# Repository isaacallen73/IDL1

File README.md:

# _Sample project_

(See the README.md file in the upper level 'examples' directory for more information about examples.)

This is the simplest buildable example. The example is used by command `idf.py create-project`
that copies the project to user specified path and set it's name. For more information follow the [docs page](https://docs.espressif.com/projects/esp-idf/en/latest/api-guides/build-system.html#start-a-new-project)

## How to use example
We encourage the users to use the example as a template for the new projects.
A recommended way is to follow the instructions on a [docs page](https://docs.espressif.com/projects/esp-idf/en/latest/api-guides/build-system.html#start-a-new-project).

## Example folder contents

The project **sample_project** contains one source file in C language [main.c](main/main.c). The file is located in folder [main](main).

ESP-IDF projects are built using CMake. The project build configuration is contained in `CMakeLists.txt`
files that provide set of directives and instructions describing the project's source files and targets
(executable, library, or both). 

Below is short explanation of remaining files in the project folder.

```
├── CMakeLists.txt
├── main
│   ├── CMakeLists.txt
│   └── main.c
└── README.md                  This is the file you are currently reading
```
Additionally, the sample project contains Makefile and component.mk files, used for the legacy Make based build system. 
They are not used or needed when building with CMake and idf.py.

## Android app

This repository also contains an Android application in the `android-app/` folder. The Android project is included for convenience and should be built from Android Studio or the Gradle wrapper.

- Do NOT commit `local.properties` or keystore files (`*.jks`, `*.keystore`). A project-level `.gitignore` is present to prevent accidental commits of these files.
- To build locally, create `local.properties` (not checked in) containing your Android SDK path, for example:

```
sdk.dir=C:/Users/isaac/AppData/Local/Android/Sdk
```

- Open the `android-app` folder in Android Studio or run the Gradle wrapper from the `android-app` folder:

```powershell
cd android-app
.\gradlew assembleDebug
```

- The repo-level `.gitignore` ignores `android-app/build/` and other generated files.

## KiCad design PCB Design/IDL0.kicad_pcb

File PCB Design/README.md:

# PCB Design for Mountain Bike Datalogger

This directory contains everything needed to design and manufacture the PCB for the mountain bike datalogger project.

---

## Quick Links

| Document | Purpose |
|----------|---------|
| **[QUICK_START.md](QUICK_START.md)** | Start here! Step-by-step guide to generate your PCB |
| **[PROGRAMMATIC_PCB_TOOLS.md](PROGRAMMATIC_PCB_TOOLS.md)** | Complete research on CLI/Python PCB tools |
| **[pnan.md](pnan.md)** | Complete circuit specification and netlist |
| **[KICAD_WORKFLOW.md](KICAD_WORKFLOW.md)** | Manual KiCad design workflow |
| **[DESIGN_CHECKLIST.md](DESIGN_CHECKLIST.md)** | Pre-manufacturing verification checklist |

---

## What's in This Directory

### Documentation Files

1. **QUICK_START.md** - Your starting point
   - Three workflow options (automated, semi-automated, manual)
   - Step-by-step walkthrough
   - Troubleshooting guide
   - Complete from netlist generation to ordering PCBs

2. **PROGRAMMATIC_PCB_TOOLS.md** - Tool research and comparison
   - kicad-cli capabilities and examples
   - SKiDL for Python-based schematic entry
   - pcbnew Python API for PCB manipulation
   - FreeRouting autorouter integration
   - PCBflow for programmatic routing
   - PHDL hardware description language
   - Complete workflow options with pros/cons
   - Installation instructions

3. **pnan.md** - Circuit specification
   - Complete netlist and pin assignments
   - Power distribution
   - Component list
   - Connector pinouts
   - PCB layout guidelines
   - Bill of materials

4. **KICAD_WORKFLOW.md** - Manual KiCad workflow
   - Traditional PCB design process
   - Best practices for KiCad
   - Layer stack configuration
   - Design rules

5. **DESIGN_CHECKLIST.md** - Pre-manufacturing checklist
   - Component placement verification
   - Routing checks
   - DRC validation
   - Gerber export checklist

### Python Scripts

1. **generate_pcb.py** - Circuit definition and netlist generator
   - Complete datalogger circuit in SKiDL
   - Generates KiCad-compatible netlist
   - Creates component placement helper script
   - Provides workflow examples
   - **Run this first!**

2. **autoroute_example.py** - Automation and export tools
   - FreeRouting integration
   - DRC automation
   - Gerber export automation
   - Position file generation
   - 3D model export

---

## Getting Started

### Option 1: Quick Start (Recommended)

```bash
# Install dependencies
pip install skidl

# Generate circuit and netlist
python generate_pcb.py

# Follow the steps in QUICK_START.md
```

### Option 2: Read First, Then Build

1. Read **PROGRAMMATIC_PCB_TOOLS.md** to understand the tools
2. Review **pnan.md** to understand the circuit
3. Follow **QUICK_START.md** for step-by-step instructions

### Option 3: Traditional Workflow

1. Read **KICAD_WORKFLOW.md**
2. Use **pnan.md** as reference
3. Design manually in KiCad GUI
4. Use **DESIGN_CHECKLIST.md** before ordering

---

## Workflow Comparison

### Fully Automated (Experimental)
- **Tools**: SKiDL + pcbnew API + FreeRouting + kicad-cli
- **Automation**: ~80%
- **Quality**: Good
- **Time**: 1-2 hours
- **Best for**: Simple boards, rapid prototyping, learning

### Semi-Automated (Recommended)
- **Tools**: SKiDL + Manual KiCad + FreeRouting + kicad-cli
- **Automation**: ~40%
- **Quality**: Excellent
- **Time**: 2-4 hours
- **Best for**: Production boards, this datalogger

### Manual with Scripts
- **Tools**: SKiDL (netlist only) + Manual KiCad + kicad-cli
- **Automation**: ~20%
- **Quality**: Excellent
- **Time**: 4-6 hours
- **Best for**: Learning KiCad, complex boards

---

## File Outputs

When you run `generate_pcb.py`, it creates:

```
output/
├── datalogger.net          # KiCad netlist (import to PCBNew)
├── place_components.py     # Component placement script
└── README.txt              # Next steps

```

When you run `autoroute_example.py export`, it creates:

```
output/
├── gerbers/
│   ├── *.gbr               # Gerber files (one per layer)
│   ├── *.drl               # Drill files
│   └── *-job.gbrjob        # Gerber job file
├── datalogger_pos.csv      # Component position file
├── datalogger.step         # 3D STEP model
└── drc_report.txt          # Design rule check report
```

---

## Key Technologies Used

### 1. SKiDL (Schematic Capture)
Python package for circuit definition
- Website: https://devbisme.github.io/skidl/
- GitHub: https://github.com/devbisme/skidl
- Install: `pip install skidl`

### 2. KiCad (PCB Design)
Open-source EDA software
- Website: https://www.kicad.org/
- Docs: https://docs.kicad.org/
- Version: 8.0 or 9.0 recommended

### 3. kicad-cli (Command Line Interface)
Built into KiCad 7+
- Export Gerbers
- Run DRC
- Generate documentation
- No separate installation needed

### 4. FreeRouting (Autorouter)
Open-source PCB autorouter
- Website: https://freerouting.org/
- GitHub: https://github.com/freerouting/freerouting
- Install: Via KiCad Plugin Manager

### 5. pcbnew Python API (Optional)
KiCad's Python scripting interface
- Built into KiCad
- Cross-version wrapper: `pip install kicad-python`
- Docs: https://dev-docs.kicad.org/

---

## Circuit Overview

**Main Components:**
- Seeed XIAO ESP32-C6 (microcontroller)
- 3x BMI160 IMU (onboard + front + rear)
- NEO-6M GPS module
- microSD card slot
- JST battery connector
- 3x waterproof connectors (front, rear, handlebar)

**Key Features:**
- SPI bus for sensors and SD card
- UART for GPS
- Analog inputs for pressure sensors
- GPIO for buttons and LED
- Complete power distribution with decoupling

**Board Size:** ~60mm x 40mm (adjust to battery)

**Layers:** 2 (top copper + bottom ground plane)

See [pnan.md](pnan.md) for complete specifications.

---

## Next Steps

1. **Generate netlist**
   ```bash
   python generate_pcb.py
   ```

2. **Import to KiCad**
   - Open KiCad PCBNew
   - Tools → Load Netlist
   - Select `output/datalogger.net`

3. **Place components**
   - Manual placement (recommended)
   - Or use `output/place_components.py`

4. **Route board**
   - Manual critical traces
   - FreeRouting for remainder

5. **Export Gerbers**
   ```bash
   python autoroute_example.py export datalogger.kicad_pcb
   ```

6. **Order PCBs**
   - Upload Gerbers to JLCPCB, PCBWay, or OSH Park
   - ~$5-20 for 5 boards
   - 1-2 week delivery

---

## Troubleshooting

**"SKiDL not found"**
```bash
pip install skidl
```

**"kicad-cli not found"**
- Install KiCad 7+
- Add KiCad to system PATH

**"pcbnew module not found"**
- KiCad must be installed
- pcbnew is part of KiCad, not a separate package

**"FreeRouting can't route"**
- Check component placement (too tight?)
- Route critical traces manually first
- Increase board size if needed

See **QUICK_START.md** for detailed troubleshooting.

---

## Tools Research Summary

Based on extensive research of 2025 PCB design tools:

### ✓ Recommended Tools
1. **kicad-cli** - Excellent for exports (Gerbers, DRC)
2. **SKiDL** - Best for schematic/netlist generation
3. **pcbnew API** - Good for component placement
4. **FreeRouting** - Reliable autorouter with Python API
5. **kicad-python** - Wrapper for cross-version compatibility

### ⚠ Experimental Tools
1. **PCBflow** - Promising but alpha quality
2. **OrthoRoute** - New GPU-accelerated router

### ✗ Not Recommended
1. **PHDL** - Older, less active (use SKiDL instead)

See **PROGRAMMATIC_PCB_TOOLS.md** for detailed analysis.

---

## Can You Generate a PCB Fully Automatically?

### Short Answer: ~80% automated

**What CAN be automated:**
- ✓ Schematic/netlist generation (SKiDL)
- ✓ Component placement (pcbnew Python API)
- ✓ Autorouting (FreeRouting)
- ✓ DRC (kicad-cli)
- ✓ Gerber export (kicad-cli)

**What still needs human input:**
- ✗ Complex component placement optimization
- ✗ Critical trace routing (power, high-speed signals)
- ✗ Mechanical considerations (mounting holes, enclosures)
- ✗ Design verification and quality checks

**Realistic workflow:** Generate 80% automatically, manually refine the critical 20%

---

## Resources

### Official Documentation
- [KiCad Documentation](https://docs.kicad.org/)
- [SKiDL Documentation](https://devbisme.github.io/skidl/)
- [FreeRouting Docs](https://freerouting.org/)
- [KiCad Python API](https://dev-docs.kicad.org/en/apis-and-binding/pcbnew/)

### Community
- [KiCad Forum](https://forum.kicad.info/)
- [SKiDL GitHub](https://github.com/devbisme/skidl)
- [r/PrintedCircuitBoard](https://reddit.com/r/PrintedCircuitBoard)
- [EEVblog Forum](https://www.eevblog.com/forum/)

### Tutorials
- [Automating PCB Workflows](https://www.prasunbarua.com/2025/04/automating-pcb-design-workflows-with.html)
- [Programmatic Layout Tutorial](https://jeffmcbride.net/programmatic-layout-with-kicad-and-python/)
- [SKiDL on Hackaday](https://hackaday.com/2016/12/28/skidl-script-your-circuits-in-python/)

### Example Projects
- [SKiDL Examples](https://github.com/devbisme/skidl/tree/master/examples)
- [PCBflow Examples](https://github.com/michaelgale/pcbflow/tree/main/examples)

---

## Contributing

Found an issue or have improvements?
1. Test your changes
2. Update relevant documentation
3. Submit changes

---

## License

This project is part of the ESP32 Datalogger v2 project.
See main repository for license information.

---

## Changelog

### 2025-12-21
- Initial research on programmatic PCB design tools
- Created comprehensive documentation
- Implemented SKiDL circuit definition
- Added automation scripts for routing and export
- Created quick start guide

---

**Ready to build your PCB?** Start with [QUICK_START.md](QUICK_START.md)!

**Want to understand the tools?** Read [PROGRAMMATIC_PCB_TOOLS.md](PROGRAMMATIC_PCB_TOOLS.md)!

**Need circuit details?** Check [pnan.md](pnan.md)!

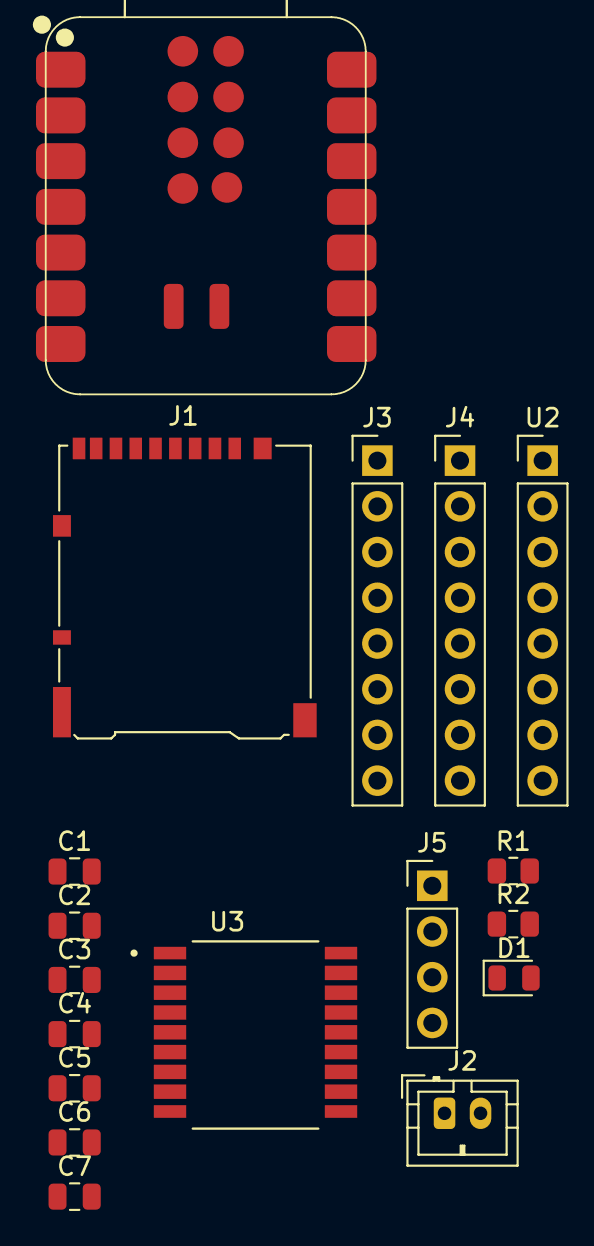
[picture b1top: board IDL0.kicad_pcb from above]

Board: 2 copper layers, 18 parts (0 on the bottom side), 17 nets, no tracks yet.

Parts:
C1, C2, C3, C4, C5, C6, C7: 10uF; C_0805_2012Metric
D1: Green; LED_0805_2012Metric
J1: MicroSD; microSD_HC_Hirose_DM3AT-SF-PEJM5
J2: JST-PH-2.0mm; JST_PH_B2B-PH-K_1x02_P2.00mm_Vertical
J3: FRONT; PinHeader_1x08_P2.54mm_Vertical
J4: REAR; PinHeader_1x08_P2.54mm_Vertical
J5: HANDLEBAR; PinHeader_1x04_P2.54mm_Vertical
R1: 10k; R_0805_2012Metric
R2: 1k; R_0805_2012Metric
U1: XIAO_ESP32-C6; XIAO-ESP32C6-SMD
U2: BMI160_Breakout; PinHeader_1x08_P2.54mm_Vertical
U3: M10S; XCVR_MAX-M10S-00B

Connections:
+3V3: C1.1, C2.1, C3.1, C4.1, C5.1, C6.1, C7.1, D1.2, J1.1, J3.1, J4.1, R1.2, U1.14, U2.1, U3.1
BUTTON_PWR: J5.2, R1.1, U1.11
CS_BMI_FRONT: J3.6, U1.5
CS_BMI_ONBOARD: U1.4, U2.6
CS_BMI_REAR: J4.6, U1.6
CS_SD: J1.6, U1.7
GND: C1.2, C2.2, C3.2, C4.2, C5.2, C6.2, C7.2, J1.2, J2.2, J3.2, J4.2, J5.1, R2.2, U1.15, U1.17, U2.2, U3.2
GPS_RX: U1.8, U3.4
GPS_TX: U1.9, U3.3
LED_STATUS: J5.4, U1.10
unnamed: D1.1, R2.1
PRESSURE_FRONT: J3.7, U1.12
PRESSURE_REAR: J4.7, U1.13
SPI_MISO: J1.4, J3.4, J4.4, U1.2, U2.5
SPI_MOSI: J1.5, J3.5, J4.5, U1.3, U2.4
SPI_SCK: J1.3, J3.3, J4.3, U1.1, U2.3
VBAT: J2.1, U1.16

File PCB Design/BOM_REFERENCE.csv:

Reference,Quantity,Component,Value,Footprint,Supplier,Part Number,Notes,Estimated Cost
U1,1,XIAO ESP32-C6,-,Custom (castellated pads),Seeed,113991054,Main microcontroller,$7.00
U2,1,BMI160,-, LGA-14 or breakout,Bosch,BMI160,On-board IMU - recommend breakout for first build,$5.00
U3,1,NEO-6M GPS Module,-,Module,u-blox,NEO-6M,GPS module with antenna connector,$10.00
J1,1,MicroSD Card Slot,-,microSD_HC_Hirose_DM3AT,Hirose,DM3AT-SF-PEJM5,Push-push type,$2.00
J2,1,JST Battery Connector,2-pin,JST_PH_B2B-PH-K_1x02_P2.00mm,JST,B2B-PH-K-S,2.0mm pitch right-angle,$1.00
J3,1,Front Connector,8-pin,Header or waterproof,TE/Molex,TBD,Waterproof recommended - select based on harness design,$3.00
J4,1,Rear Connector,8-pin,Header or waterproof,TE/Molex,TBD,Same as J3,$3.00
J5,1,Handlebar Connector,4-pin,Header or waterproof,TE/Molex,TBD,Can use smaller connector,$2.00
C1,1,Capacitor,10µF,0805,Murata/Samsung,GRM21BR71A106KE51L,X7R 10V+ XIAO power,$0.20
C2,1,Capacitor,10µF,0805,Murata/Samsung,GRM21BR71A106KE51L,X7R 10V+ BMI160,$0.20
C3,1,Capacitor,10µF,0805,Murata/Samsung,GRM21BR71A106KE51L,X7R 10V+ GPS,$0.20
C4,1,Capacitor,10µF,0805,Murata/Samsung,GRM21BR71A106KE51L,X7R 10V+ SD card,$0.20
C5,1,Capacitor,10µF,0805,Murata/Samsung,GRM21BR71A106KE51L,X7R 10V+ Front connector,$0.20
C6,1,Capacitor,10µF,0805,Murata/Samsung,GRM21BR71A106KE51L,X7R 10V+ Rear connector,$0.20
C7,1,Capacitor,10µF,0805,Murata/Samsung,GRM21BR71A106KE51L,X7R 10V+ Handlebar connector,$0.20
R1,1,Resistor,10kΩ,0805,Yageo,RC0805FR-0710KL,1% tolerance button pull-up,$0.10
R2,1,Resistor,1kΩ,0805,Yageo,RC0805FR-071KL,1% tolerance power LED,$0.10
R3,1,Resistor,220Ω,0805,Yageo,RC0805FR-07220RL,1% tolerance status LED (on harness),$0.10
D1,1,LED,Green,0805 or 3mm THT,Lite-On,LTST-C170GKT,Power indicator - green,$0.30
ANT1,1,GPS Antenna Connector,U.FL or SMA,U.FL or SMA,Various,TBD,For external GPS antenna (optional),$2.00
,,,,,,,Total Components:,$37.20
,,,,,,,PCBs (5x from JLCPCB):,$25.00
,,,,,,,Grand Total:,$62.20

External Harness Components (not on main board):
Reference,Quantity,Component,Value,Notes,Estimated Cost
U4,1,BMI160,Breakout,Front harness IMU,$5.00
U5,1,BMI160,Breakout,Rear harness IMU,$5.00
SENS1,1,Pressure Sensor,Analog 0-3.3V,Front fork pressure,$15.00
SENS2,1,Pressure Sensor,Analog 0-3.3V,Rear shock pressure,$15.00
BTN1,1,Momentary Button,SPST NO,Power ON button,$1.00
BTN2,1,Momentary Button,SPST NO,Power OFF button (future),$1.00
LED2,1,LED,Any color 3mm,Status LED on handlebar,$0.50
CABLE,3,Cable,Multi-conductor,Waterproof cable 18-22AWG,$20.00
CONN,6,Mating Connectors,Match J3/J4/J5,Male connectors for harnesses,$10.00
,,,,,Harness Total:,$72.50

Notes:
- All capacitors should be X7R or X5R ceramic with 10V+ rating
- Resistors 1% tolerance 1/8W or higher
- Consider buying extras (caps/resistors) as they're easy to lose
- BMI160 breakout boards are easier to solder for beginners
- GPS module typically includes antenna - external antenna optional
- Waterproof connectors recommended for bike application (wet conditions)
- Use marine-grade heat shrink for harness weatherproofing

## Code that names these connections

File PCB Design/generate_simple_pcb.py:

#!/usr/bin/env python3
"""
Simplified PCB Generation for Mountain Bike Datalogger
Uses only built-in SKiDL components to avoid library dependency issues
"""

from skidl import *
import os

# Set KiCad library path
os.environ['KICAD9_SYMBOL_DIR'] = r'C:\Program Files\KiCad\9.0\share\kicad\symbols'

# Set default tool
set_default_tool(KICAD8)

print("=" * 70)
print("Mountain Bike Datalogger - Simplified PCB Generation")
print("=" * 70)

print("\n[Step 1] Creating circuit definition with SKiDL...")

# Define nets
gnd = Net('GND')
vcc_3v3 = Net('+3V3')
vbat = Net('VBAT')

# SPI bus nets
spi_sck = Net('SPI_SCK')
spi_miso = Net('SPI_MISO')
spi_mosi = Net('SPI_MOSI')

# Chip select nets
cs_bmi_onboard = Net('CS_BMI_ONBOARD')
cs_bmi_front = Net('CS_BMI_FRONT')
cs_bmi_rear = Net('CS_BMI_REAR')
cs_sd = Net('CS_SD')

# UART nets
gps_tx = Net('GPS_TX')
gps_rx = Net('GPS_RX')

# GPIO nets
led_status = Net('LED_STATUS')
button_pwr = Net('BUTTON_PWR')

# Analog nets
pressure_front = Net('PRESSURE_FRONT')
pressure_rear = Net('PRESSURE_REAR')

print("Creating connectors and components...")

# XIAO ESP32-C6 - Represented as a 17-pin connector
mcu = Part('Connector_Generic', 'Conn_01x17', ref='U1', value='XIAO_ESP32-C6',
           footprint='Connector_PinHeader_2.54mm:PinHeader_1x17_P2.54mm_Vertical')

# Assign pins
mcu[1] += spi_sck        # D0 - GPIO0
mcu[2] += spi_miso       # D1 - GPIO1
mcu[3] += spi_mosi       # D2 - GPIO2
mcu[4] += cs_bmi_onboard # D3 - GPIO3
mcu[5] += cs_bmi_front   # D4 - GPIO4
mcu[6] += cs_bmi_rear    # D5 - GPIO5
mcu[7] += cs_sd          # D6 - GPIO6
mcu[8] += gps_rx         # D7 - GPIO7 (MCU RX, from GPS TX)
mcu[9] += gps_tx         # D8 - GPIO20 (MCU TX, to GPS RX)
mcu[10] += led_status    # D9 - GPIO21
mcu[11] += button_pwr    # D10 - GPIO8
mcu[12] += pressure_front # A0 - GPIO22
mcu[13] += pressure_rear  # A2 - GPIO23
mcu[14] += vcc_3v3       # 3V3
mcu[15] += gnd           # GND
mcu[16] += vbat          # BAT+
mcu[17] += gnd           # BAT-

# BMI160 IMU (onboard) - Represented as generic IC
imu = Part('Connector_Generic', 'Conn_01x08', ref='U2', value='BMI160',
           footprint='Package_LGA:LGA-14_3x2.5mm_P0.5mm')
imu[1] += vcc_3v3
imu[2] += gnd
imu[3] += spi_sck
imu[4] += spi_mosi
imu[5] += spi_miso
imu[6] += cs_bmi_onboard
imu[7] += NC  # INT1
imu[8] += NC  # INT2

# GPS Module
gps = Part('Connector_Generic', 'Conn_01x04', ref='U3', value='NEO-6M',
           footprint='RF_GPS:ublox_NEO')
gps[1] += vcc_3v3
gps[2] += gnd
gps[3] += gps_tx  # GPS TX to MCU RX
gps[4] += gps_rx  # GPS RX from MCU TX

# MicroSD Card
sd = Part('Connector_Generic', 'Conn_01x06', ref='J1', value='MicroSD',
          footprint='Connector_Card:microSD_HC_Hirose_DM3AT-SF-PEJM5')
sd[1] += vcc_3v3
sd[2] += gnd
sd[3] += spi_sck
sd[4] += spi_miso
sd[5] += spi_mosi
sd[6] += cs_sd

print("Adding passive components...")

# Decoupling capacitors
for i, (ref, desc) in enumerate([
    ('C1', 'XIAO'),
    ('C2', 'BMI160'),
    ('C3', 'GPS'),
    ('C4', 'SD'),
    ('C5', 'Front'),
    ('C6', 'Rear'),
    ('C7', 'Handlebar')
], 1):
    cap = Part('Device', 'C', ref=ref, value='10uF',
               footprint='Capacitor_SMD:C_0805_2012Metric')
    cap[1] += vcc_3v3
    cap[2] += gnd

# Resistors
r1 = Part('Device', 'R', ref='R1', value='10k',
          footprint='Resistor_SMD:R_0805_2012Metric')
r1[1] += button_pwr
r1[2] += vcc_3v3

r2 = Part('Device', 'R', ref='R2', value='1k',
          footprint='Resistor_SMD:R_0805_2012Metric')

r3 = Part('Device', 'R', ref='R3', value='220',
          footprint='Resistor_SMD:R_0805_2012Metric')

# LEDs
led = Part('Device', 'LED', ref='D1', value='Green',
           footprint='LED_SMD:LED_0805_2012Metric')
led['A'] += vcc_3v3
led['K'] += r2[1]
r2[2] += gnd

print("Creating external connectors...")

# Battery connector
batt = Part('Connector', 'Conn_01x02', ref='J2', value='JST-PH-2.0mm',
            footprint='Connector_JST:JST_PH_B2B-PH-K_1x02_P2.00mm_Vertical')
batt[1] += vbat
batt[2] += gnd

# Front connector
front = Part('Connector_Generic', 'Conn_01x08', ref='J3', value='FRONT',
             footprint='Connector_PinHeader_2.54mm:PinHeader_1x08_P2.54mm_Vertical')
front[1] += vcc_3v3
front[2] += gnd
front[3] += spi_sck
front[4] += spi_miso
front[5] += spi_mosi
front[6] += cs_bmi_front
front[7] += pressure_front
front[8] += NC  # Hall sensor (future)

# Rear connector
rear = Part('Connector_Generic', 'Conn_01x08', ref='J4', value='REAR',
            footprint='Connector_PinHeader_2.54mm:PinHeader_1x08_P2.54mm_Vertical')
rear[1] += vcc_3v3
rear[2] += gnd
rear[3] += spi_sck
rear[4] += spi_miso
rear[5] += spi_mosi
rear[6] += cs_bmi_rear
rear[7] += pressure_rear
rear[8] += NC  # Hall sensor (future)

# Handlebar connector
handlebar = Part('Connector_Generic', 'Conn_01x04', ref='J5', value='HANDLEBAR',
                 footprint='Connector_PinHeader_2.54mm:PinHeader_1x04_P2.54mm_Vertical')
handlebar[1] += gnd
handlebar[2] += button_pwr
handlebar[3] += NC  # Second button (future)
handlebar[4] += led_status

print("Circuit definition complete!")

# Generate netlist
print("\n[Step 2] Generating netlist...")
os.makedirs('output', exist_ok=True)

netlist_file = 'output/datalogger.net'
generate_netlist(file_=netlist_file)

print(f"✓ Netlist generated: {netlist_file}")

# Generate ERC report
print("\n[Step 3] Running Electrical Rules Check...")
try:
    erc()
    print("✓ ERC passed!")
except Exception as e:
    print(f"⚠ ERC warnings/errors (review manually): {e}")

# Generate component placement script
print("\n[Step 4] Generating component placement script...")

placement_script = '''#!/usr/bin/env python3
"""
Component Placement Script for Datalogger PCB
Run this inside KiCad PCBNew scripting console
"""

import pcbnew

board = pcbnew.GetBoard()

# Component placements (x, y in mm, rotation in degrees)
placements = {
    'U1': (30, 20, 0),    # XIAO center
    'U2': (20, 18, 0),    # BMI160 left of XIAO
    'U3': (50, 30, 0),    # GPS upper right
    'J1': (10, 30, 90),   # SD card left edge
    'J2': (35, 10, 0),    # Battery near XIAO
    'J3': (5, 5, 0),      # Front connector bottom left
    'J4': (55, 5, 0),     # Rear connector bottom right
    'J5': (30, 38, 0),    # Handlebar top center
    'C1': (32, 18, 0),    # Near XIAO
    'C2': (18, 16, 0),    # Near BMI160
    'C3': (52, 28, 0),    # Near GPS
    'C4': (8, 28, 0),     # Near SD
    'R1': (28, 36, 0),    # Near handlebar
    'R2': (42, 20, 0),    # Near XIAO
    'D1': (42, 22, 0),    # Power LED
}

for ref, (x, y, rot) in placements.items():
    fp = board.FindFootprintByReference(ref)
    if fp:
        fp.SetPosition(pcbnew.VECTOR2I(pcbnew.FromMM(x), pcbnew.FromMM(y)))
        fp.SetOrientationDegrees(rot)
        print(f"Placed {ref} at ({x}, {y})")
    else:
        print(f"Warning: {ref} not found")

pcbnew.Refresh()
print("Placement complete!")
'''

with open('output/place_components.py', 'w') as f:
    f.write(placement_script)

print("✓ Placement script: output/place_components.py")

# Generate SVG schematic
print("\n[Step 5] Generating schematic SVG...")
try:
    generate_svg(file_='output/schematic.svg')
    print("✓ Schematic SVG: output/schematic.svg")
except:
    print("⚠ SVG generation skipped (optional)")

print("\n" + "=" * 70)
print("SUCCESS! Files generated:")
print("=" * 70)
print("\n✓ output/datalogger.net - KiCad netlist")
print("✓ output/place_components.py - Component placement script")
print("✓ output/schematic.svg - Circuit diagram (if generated)")

print("\n" + "=" * 70)
print("NEXT STEPS:")
print("=" * 70)
print("""
1. Open KiCad PCBNew
2. Create new PCB project
3. Tools → Load Netlist → Select output/datalogger.net
4. All components will appear on the canvas

5. Run placement script:
   - Tools → Scripting Console
   - Paste contents of output/place_components.py
   - Or: File → Open → output/place_components.py

6. Route the board:
   - Manual routing (recommended for first PCB)
   - OR: Tools → External Tools → FreeRouting

7. Add ground plane:
   - Right toolbar → Add Filled Zone
   - Draw around board edge
   - Net: GND, Layer: B.Cu

8. Run DRC:
   - Inspect → Design Rules Checker
   - Fix any errors

9. Export Gerbers:
   - File → Fabrication Outputs → Gerbers
   - Select all layers, generate

10. Order PCBs from JLCPCB, OSH Park, or PCBWay

Board size suggestion: 60mm x 40mm
Mounting holes: 3mm diameter, M3 screws
""")

print("=" * 70)
print("Good luck with your first PCB! 🚴‍♂️")
print("=" * 70)

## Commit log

2025-11-25 Initial working state
2025-11-27 Add high-speed IMU polling (3.4kHz) with buffered SD card logging
    Features implemented:
    - BMI160 IMU polling at 3.4kHz via I2C multiplexer (PCA9548A)
    - FreeRTOS queue-based buffered architecture (64-sample queue)
    - Batch writes to SD card (256 samples per batch)
    - GPS module support with NMEA logging to SD card
    - Modular feature flags for easy configuration
2025-11-28 Got BLE working!
2025-11-29 Add VS Code workspace and Android .gitignore entries
2025-11-29 Add Android app and README notes
2025-11-29 Add Android app files
2025-11-29 Got another android app working.
2025-11-30 .csv has real data now.
2025-12-01 Stabilized gps reporting rate.
2025-12-09 3 IMUs
2025-12-12 broken but working
2025-12-13 ble still broken, but at least sd seems to work
2025-12-20 wifi transfer working
2025-12-20 Added on/off buttons
2025-12-21 fixed delete and reduced sd vebosity
2025-12-24 fucked
